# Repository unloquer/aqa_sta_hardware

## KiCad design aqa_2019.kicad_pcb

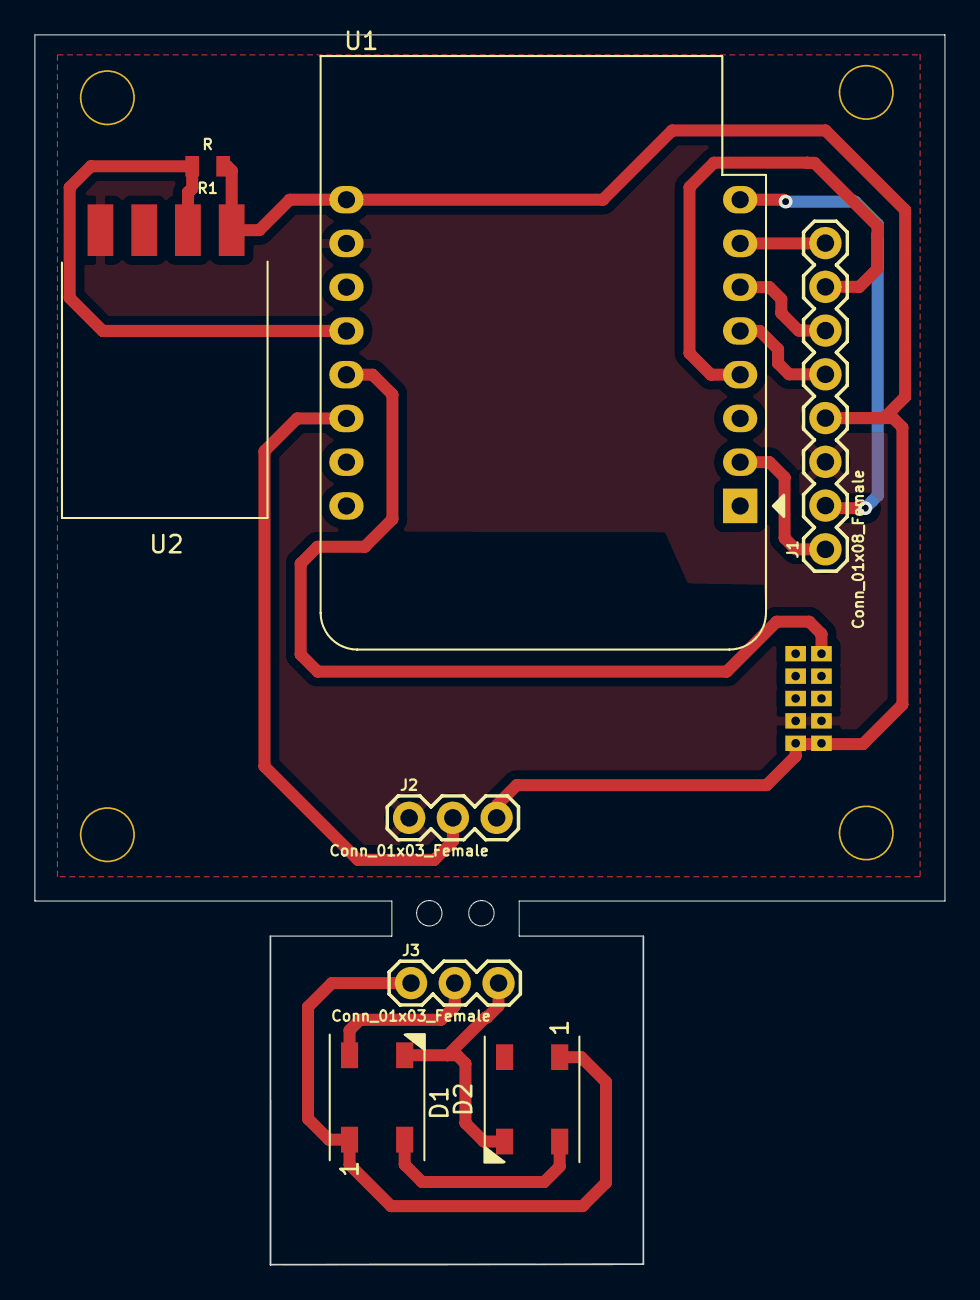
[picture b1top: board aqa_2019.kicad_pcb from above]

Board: 2 copper layers, 52.8 x 71.4 mm, 15 parts (1 on the bottom side), 12 nets.

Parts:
>NAME: >VALUE; 1X01_POGOPIN_HOLE_0.58_DIA
>NAME#2: >VALUE; 1X01_POGOPIN_HOLE_0.58_DIA
D1, D2: WS2812B; LED_WS2812B_PLCC4_5.0x5.0mm_P3.2mm
J1: Conn_01x08_Female; 1X08
J2, J3: Conn_01x03_Female; 1X03
R1: R; 0805
Ref**: Val**; PAD.03X.04
Ref**#2, Ref**#3, Ref**#4: Val**; PAD.03X.04
U1: WeMos_D1_mini; WEMOS_D1_mini_light
U2: DHT11
U3: PMS7003

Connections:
+5V: D1.1, D2.1, J1.4, J2.3, J3.1, R1.1, U1.9, U2.1, U3.1, U3.2
/CS: J1.8, U1.7
/D1: D1.4, J2.2, J3.2, U1.14
/D2: U1.13, U3.9
/D3: R1.2, U1.12, U2.2
/MISO: J1.5, U1.5
/MOSI: J1.6, U1.6
/SCK: J1.7, U1.4
GND: D1.3, D2.3, J1.3, J2.1, J3.3, U1.10, U2.4, U3.3, U3.4
unnamed: D1.2, D2.4
unnamed: J1.1, U1.2
unnamed: J1.2, U1.8

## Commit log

2019-06-26 Diseño de pbc basado en wemos+pms7003 de un dispositivo tipo estación que mide el material particulado, la humedad y la temperatura
